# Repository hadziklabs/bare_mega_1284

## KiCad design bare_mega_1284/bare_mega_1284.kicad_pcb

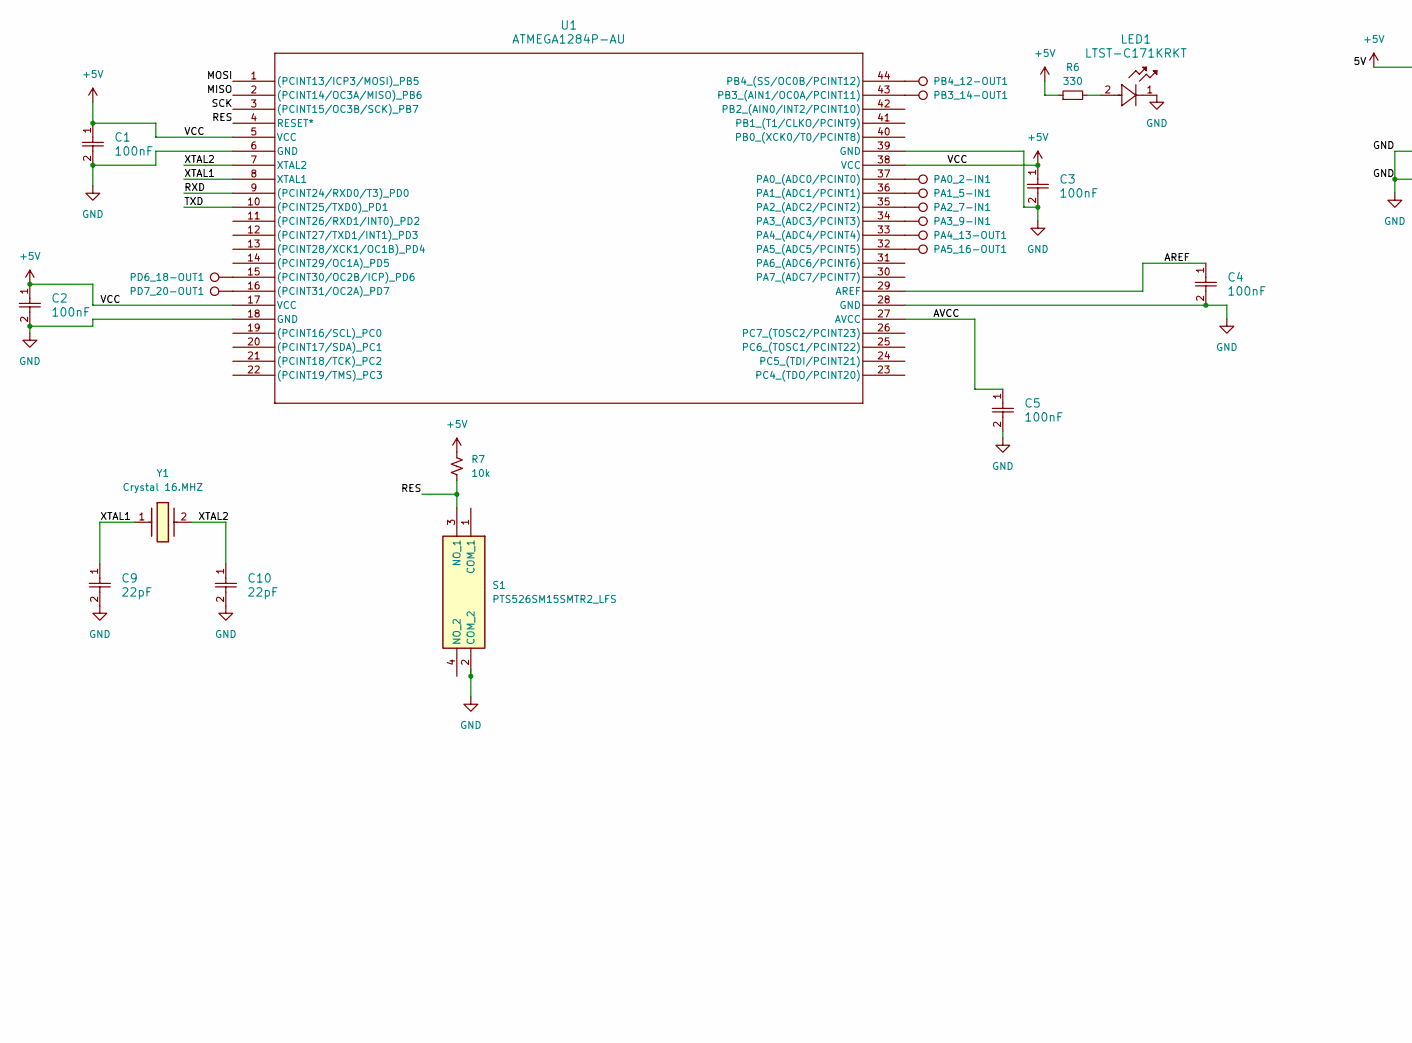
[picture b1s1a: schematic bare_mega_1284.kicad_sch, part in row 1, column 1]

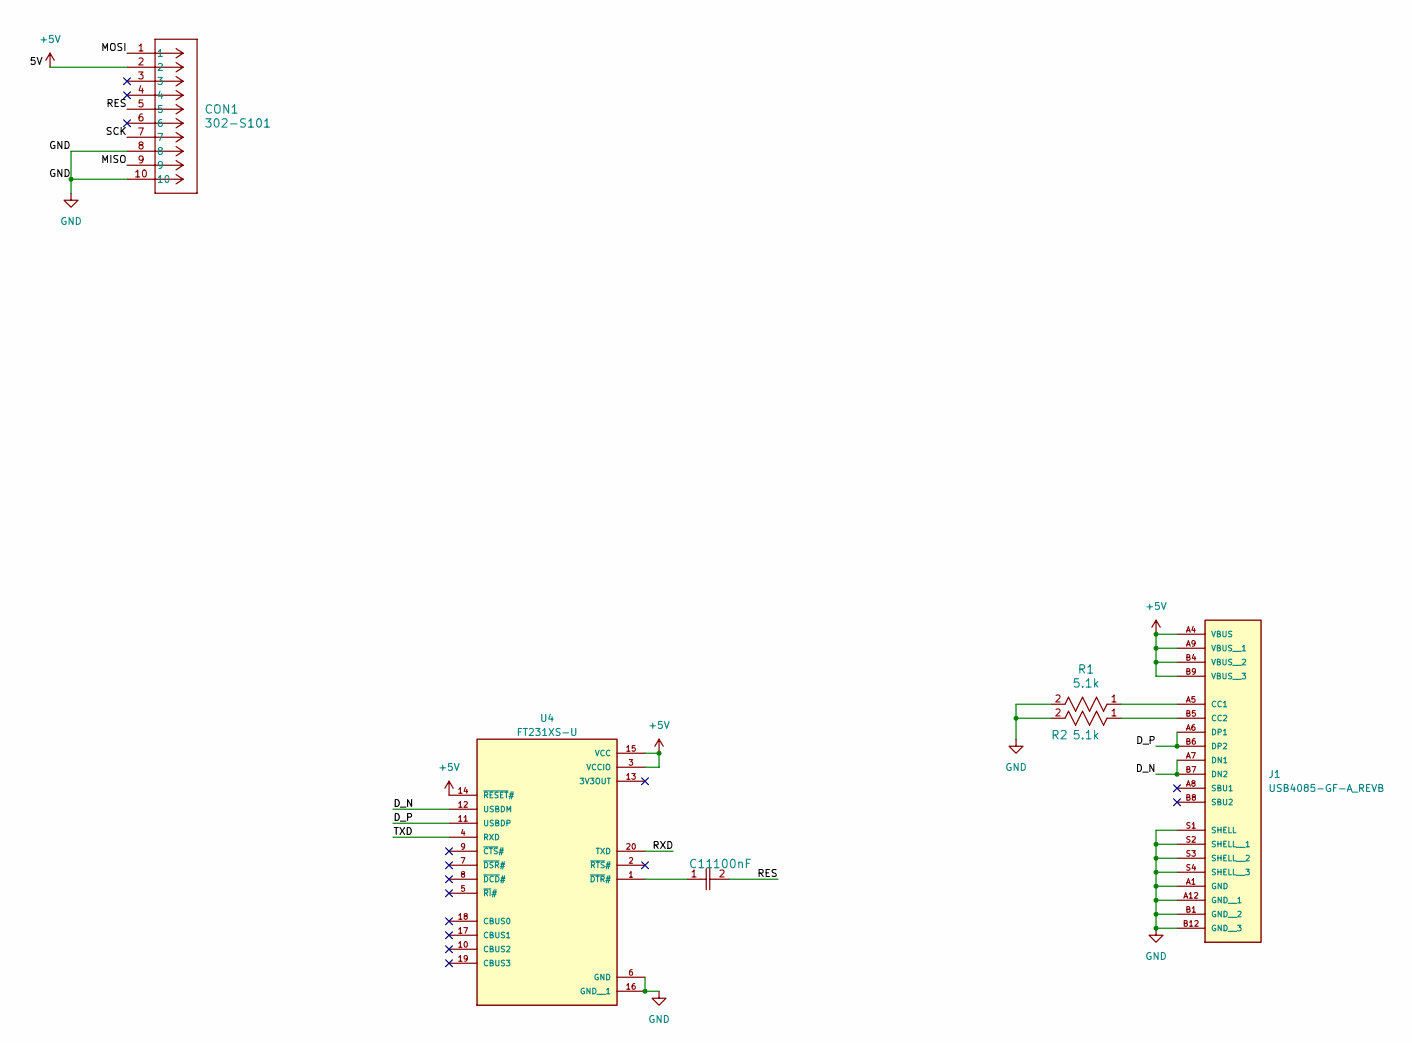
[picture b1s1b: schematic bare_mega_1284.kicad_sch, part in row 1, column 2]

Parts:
C1, C2, C3, C4, C5, C11: 100nF; CAPC340180_88N_KEM-L; part_number C1206C104K5RACTU
C9, C10: 22pF; CAPC340180_88N_KEM-L; part_number C1206C104K5RACTU
CON1: 302-S101; CONN10_302-S101_OST
J1: USB4085-GF-A_REVB; GCT_USB4085-GF-A_REVB; PARTREV B
LED1: LTST-C171KRKT; LED_RED_0805
PA0_2-IN1, PA1_5-IN1, PA2_7-IN1, PA3_9-IN1, PA4_13-OUT1, PA5_16-OUT1: TestPoint; TestPoint_Pad_2.0x2.0mm
PB3_14-OUT1, PB4_12-OUT1: TestPoint; TestPoint_Pad_2.0x2.0mm
PD6_18-OUT1, PD7_20-OUT1: TestPoint; TestPoint_Pad_2.0x2.0mm
R1, R2: 5.1k; RC0805N_YAG-L
R6: 330; R_0805_2012Metric_Pad1.20x1.40mm_HandSolder
R7: 10k; R_2010_5025Metric
S1: PTS526SM15SMTR2_LFS; small_button; Mouser Part Number 611-PTS526SM15SMTR2L
U1: ATMEGA1284P-AU; 44A_ATM
U4: FT231XS-U; USB2.0 Serial; PARTREV 1.2
Y1: Crystal 16.MHZ; Crystal 16MHz; Mouser Part Number 815-ABLS7M216MHZD2YT

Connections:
+5V: C1.1, C2.1, C3.1, CON1.2, J1.A4 (VBUS), J1.A9 (VBUS__1), J1.B4 (VBUS__2), J1.B9 (VBUS__3), R6.1, R7.1, U1.5 (VCC), U1.17 (VCC), U1.38 (VCC), U4.3 (VCCIO), U4.14 (~RESET#), U4.15 (VCC)
/AREF: C4.1, U1.29 (AREF)
/AVCC: C5.1, U1.27 (AVCC)
/D_N: J1.A7 (DN1), J1.B7 (DN2), U4.12 (USBDM)
/D_P: J1.A6 (DP1), J1.B6 (DP2), U4.11 (USBDP)
/MISO: CON1.9, U1.2 ((PCINT14/OC3A/MISO)_PB6)
/MOSI: CON1.1, U1.1 ((PCINT13/ICP3/MOSI)_PB5)
/RES: C11.2, CON1.5, R7.2, S1.3 (NO_1), U1.4 (RESET*)
/RXD: U1.9 ((PCINT24/RXD0/T3)_PD0), U4.20 (TXD)
/SCK: CON1.7, U1.3 ((PCINT15/OC3B/SCK)_PB7)
/TXD: U1.10 ((PCINT25/TXD0)_PD1), U4.4 (RXD)
/XTAL1: C9.1, U1.8 (XTAL1), Y1.1
/XTAL2: C10.1, U1.7 (XTAL2), Y1.2
GND: C1.2, C2.2, C3.2, C4.2, C5.2, C9.2, C10.2, CON1.8, CON1.10, J1.A1 (GND), J1.A12 (GND__1), J1.B1 (GND__2), J1.B12 (GND__3), J1.S1 (SHELL), J1.S2 (SHELL__1), J1.S3 (SHELL__2), J1.S4 (SHELL__3), LED1.1, R1.2, R2.2, S1.2 (COM_2), U1.6 (GND), U1.18 (GND), U1.28 (GND), U1.39 (GND), U4.6 (GND), U4.16 (GND__1)
unnamed: J1.A5 (CC1), R1.1
unnamed: J1.B5 (CC2), R2.1
unnamed: LED1.2, R6.2
unnamed: PD6_18-OUT1.1, U1.15 ((PCINT30/OC2B/ICP)_PD6)
unnamed: PD7_20-OUT1.1, U1.16 ((PCINT31/OC2A)_PD7)
unnamed: PA0_2-IN1.1, U1.37 (PA0_(ADC0/PCINT0))
unnamed: PA1_5-IN1.1, U1.36 (PA1_(ADC1/PCINT1))
unnamed: PA2_7-IN1.1, U1.35 (PA2_(ADC2/PCINT2))
unnamed: PA3_9-IN1.1, U1.34 (PA3_(ADC3/PCINT3))
unnamed: PA4_13-OUT1.1, U1.33 (PA4_(ADC4/PCINT4))
unnamed: PA5_16-OUT1.1, U1.32 (PA5_(ADC5/PCINT5))
unnamed: PB3_14-OUT1.1, U1.43 (PB3_(AIN1/OC0A/PCINT11))
unnamed: PB4_12-OUT1.1, U1.44 (PB4_(SS/OC0B/PCINT12))
unnamed: C11.1, U4.1 (~DTR#)

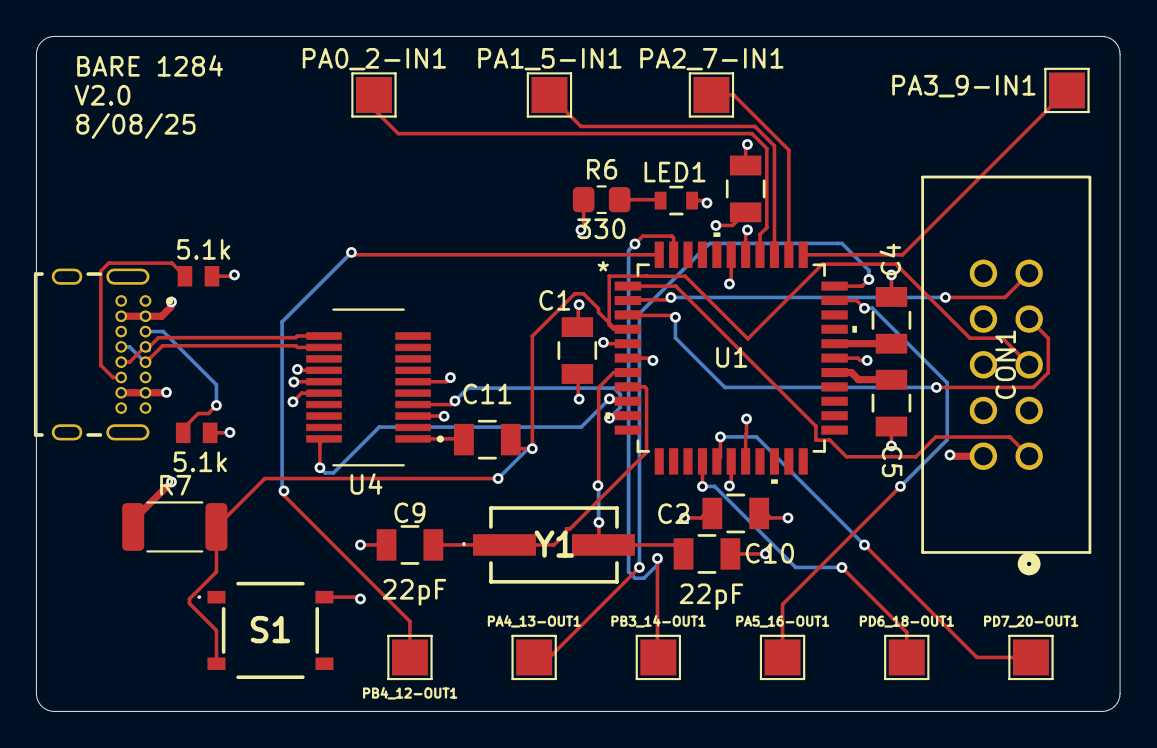
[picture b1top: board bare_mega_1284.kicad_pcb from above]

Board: 4 copper layers, 60.2 x 37.5 mm, 29 parts (0 on the bottom side), 28 nets.

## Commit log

2025-07-30 init commit
